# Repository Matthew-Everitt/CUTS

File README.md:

A toy project targetting specific hardware and use cases.

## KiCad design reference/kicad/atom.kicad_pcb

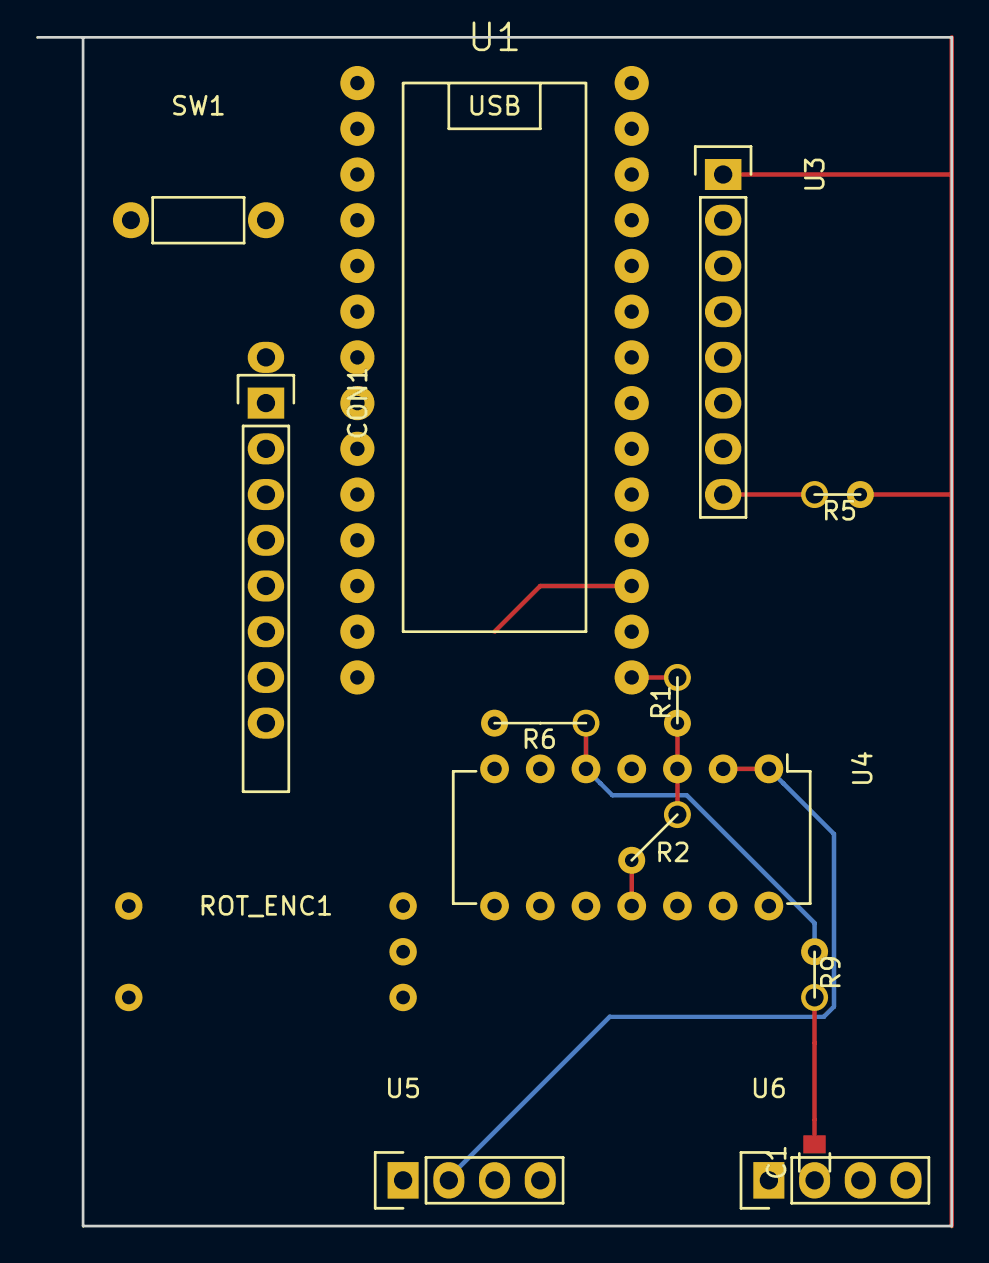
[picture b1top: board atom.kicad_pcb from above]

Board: 2 copper layers, 50.8 x 66.0 mm, 14 parts (0 on the bottom side), 24 nets.

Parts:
C1: 100n; C_0805
CON1: Backwards_SD_Card; Socket_Strip_Straight_1x09-swapped
R1, R5: R; Resistor_Breadboard
R2: R; Resistor_Breadboard-diag
R6: 100k; Resistor_Breadboard-3
R9: 10k; Resistor_Breadboard
ROT_ENC1: AB2_ROTARY_ENCODER_W_SW; RotaryEnc
SW1: BACK; Resistor_Vertical_RM7.5mm-noCircle
U1: Teensy_3.1; Teensy-3.1
U3: nokia5110; Socket_Strip_Straight_1x08
U4: TLC274; DIP-14_W7.62mm
U5, U6: monoAudio; Socket_Strip_Straight_1x04

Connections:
+3V3: CON1.4, R5.2, U1.24, U3.1, U4.4
GND: CON1.3, CON1.6, R2.2, ROT_ENC1.2, ROT_ENC1.4, SW1.1, U1.27, U3.2, U4.11, U5.1, U6.1
GNDREF: U4.8, U4.9
unnamed: C1.1, U6.2
unnamed: C1.2, R9.1
unnamed: CON1.1, U1.6
unnamed: CON1.2, U1.7
unnamed: CON1.7, U1.12
unnamed: R1.1, U1.13
unnamed: R1.2, R2.1, U4.3
unnamed: R5.1, U3.8
unnamed: R6.1, R9.2, U4.5
unnamed: R6.2, U1.15, U4.7
unnamed: SW1.2, U1.2
unnamed: U1.18, U3.7
unnamed: U1.19, U3.6
unnamed: U1.20, U3.5
unnamed: U1.21, U3.4
unnamed: U1.22, U3.3
unnamed: U4.1, U4.2, U5.2
SCLK: CON1.5, U1.14
e1: ROT_ENC1.3, U1.9
e2: ROT_ENC1.1, U1.10
eb: ROT_ENC1.5, U1.11

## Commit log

2016-06-02 Added 'getString' access helper to stdMenu, with the intention of being able to keep the same draw function, but still being able to feed it arbitary strgins rather than relying on the being in an ar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
2016-06-02 Split the 'stdMenu' into a semi-virtual base class (baseMenu_t) and an implenetation (normalMenu_t). This way we avoid the problem with getStrings where it ... doesn't work. We need it to be virtual 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
2016-06-02 Lots of messing about trying to make file listigns work. They did, but because we can't easily get a list of files we need to use openNext to walk the tree, which is very slow. Currently record last 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
2016-06-04 Cleaned up some confusion, moving things from baseMenu_t to normalMenu_t because only normalMenu_t actually needed them now that we're trying to actually read the SD card. Speaking of, yet more playi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
2016-06-04 Some formatting changes, removed redrawNeeded, fixed [const] char * warnings.
2016-06-04 Completed transition to using an array of valid indicies, added a bounds check so we only consider the first N files.
2016-06-04 Transitioned to one buffer in file class, rather than one per function.
2016-06-04 Removed benchmarking to make Serial readable again.
    Started working on being able to select files / directories.
2016-06-04 Started keeping track of the path we're in because it turns out the sdFat can't change to the parent directory.
2016-06-04 Pretty strong progress on file browsing, can now reasonably reliably enter and leave directories.
    Also noticed that the line that prepares the buffer to print the free space is missing, so the %age gets printed twice. Need to look back through comits and find the chage.
2016-06-04 Fixed free space message.
2016-06-04 Added trailing slashes to directories in the file view.
    Added some defaults to settings in settings_t
2016-06-04 Added a rough sketch of a settingsMenu class.
2016-06-04 Fixed a few bugs in th edisplay rendering, where the # of rows was miscalculated, and strings longer than 256 pixels didn't scroll.
    Some initial work on the settings page
2016-06-04 Tidied up the serial console a bit again.
2016-06-04 Settings menu working for the current three settings.
2016-06-04 Auto format everything.
2016-06-04 Added README
    Added README
2016-06-04 Replaced max and min with inferior VS friendly versions.
2016-06-04 Moved some things out of common.h to separate files, just to make things neater and easier to find.
    Fixed a bug where the number of lines used was rounded down to the closest even number.
    Added isOdd and isEven macros
2016-06-04 Removed test entries from the menu system now that we have enough actual entries.
2016-06-04 Added the outline of a new style of menu for sending files.
2016-06-04 Added a setting for named/unnamed files by default.
    Also added some new debug defines to hide some noise and commented some others out.
2016-06-04 Added a fileSend Menu type to give options. Need to implement the actual settings / file sending etc
2016-06-06 Added some hardware information.
2016-06-06 Moved all (hopefully) global variables to CUTS.ino, along with a list of referencing files.
2016-06-06 Moved the contents of nokiaDisplay.cpp to a namespace in preparation for moving it to a class. Not sure how much that will help but it does bring up some errors, which is useful.
2016-06-06 Moved display properties to a class with setup done in a constructor. Much nicer. Had to remove Serial prints from this constructor to allow it to run before Serial.begin().
2016-06-06 Removed leftover debugging sillyness.
2016-06-06 Removed the rest of it... Oops
2016-06-06 Made display_t a subclass of the actual display driver, meaning we simply have to create the one object for the display.
2016-06-06 Moved encoder object back inside display_t where it belongs.
2016-06-06 Moved displayProperties to display_t, as seems natural. Left it as a struct, which I think I prefer.
2016-06-06 Added missing hardware files
2016-06-06 Non - autosaved project files need to be committed before we can merge back into master
2016-06-29 Some kind of integration between the two projects, with proof of concept TX. RX and menus seem to work ok (no idea if changing menus etc can corrupt received files).
2016-07-07 Checkpoint - we need to split the SD storage layer from the format translation layer (namedFile, nArray etc).
